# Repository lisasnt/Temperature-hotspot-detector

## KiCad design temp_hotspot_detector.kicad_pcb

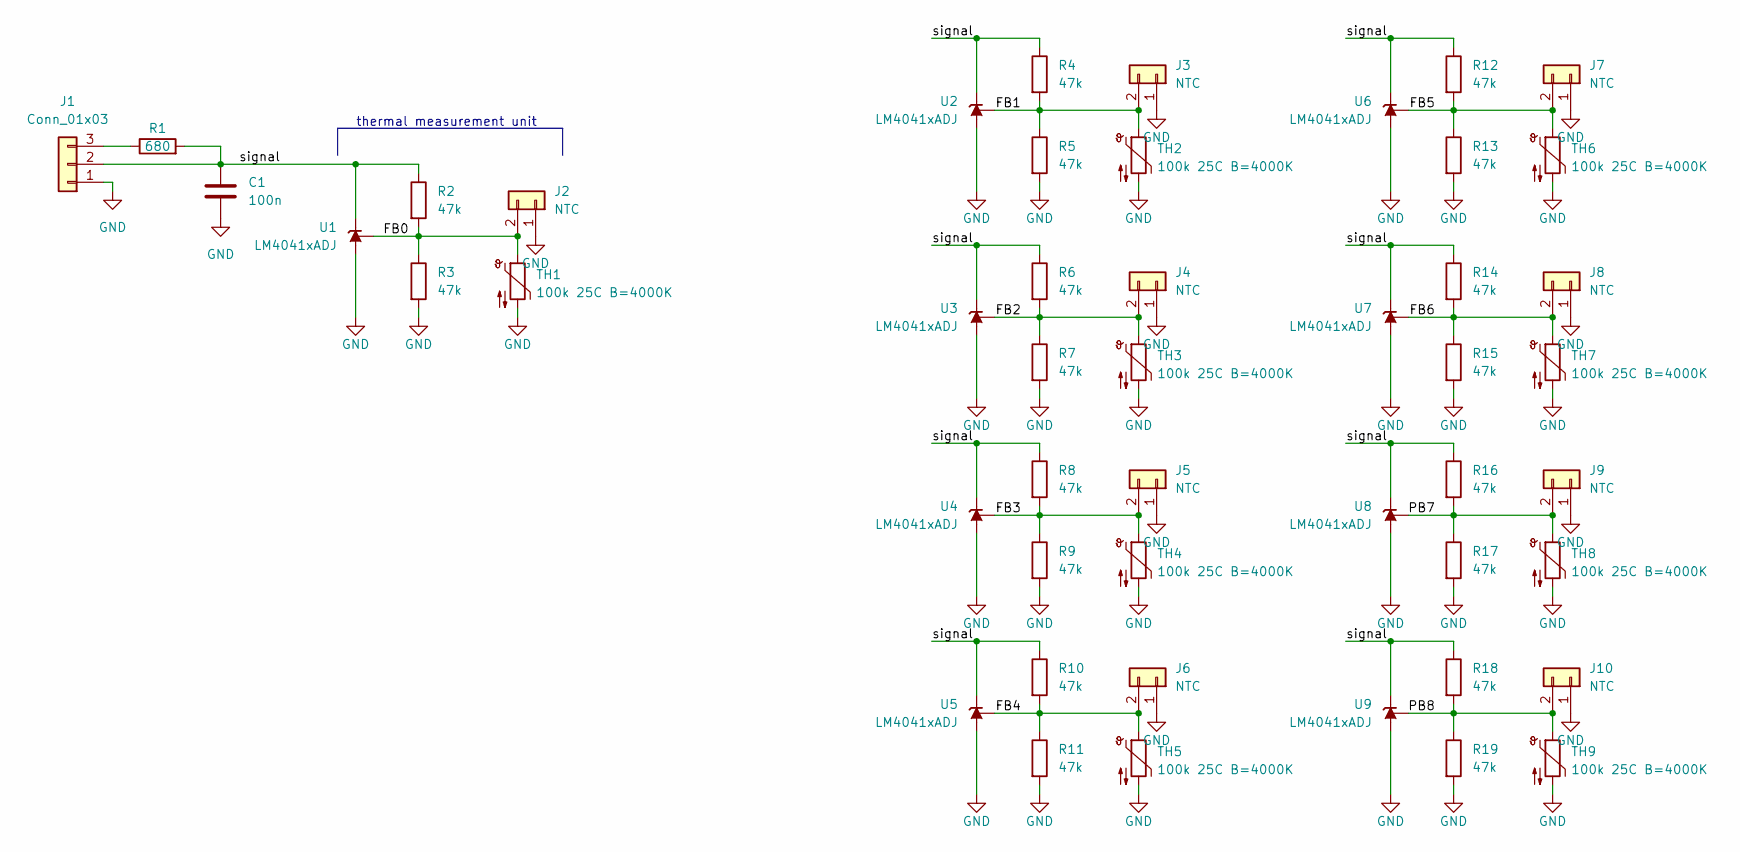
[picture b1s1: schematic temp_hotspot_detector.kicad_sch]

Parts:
C1: 100n; C_0603_1608Metric
J1: Conn_01x03; PinHeader_1x03_P2.54mm_Vertical
J2, J3, J4, J5, J6, J7, J8, J9, J10: NTC; PinHeader_1x02_P2.54mm_Vertical
R1: 680; R_0603_1608Metric
R2, R3, R4, R5, R6, R7, R8, R9, R10, R11, R12, R13, R14, R15, R16, R17, R18, R19: 47k; R_0603_1608Metric
TH1, TH2, TH3, TH4, TH5, TH6, TH7, TH8, TH9: 100k 25C B=4000K; R_0603_1608Metric
U1, U2, U3, U4, U5, U6, U7, U8, U9: LM4041xADJ; SOT-23

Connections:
/FB0: J2.2, R2.2, R3.1, TH1.1, U1.1 (REF)
/FB1: J3.2, R4.2, R5.1, TH2.1, U2.1 (REF)
/FB2: J4.2, R6.2, R7.1, TH3.1, U3.1 (REF)
/FB3: J5.2, R8.2, R9.1, TH4.1, U4.1 (REF)
/FB4: J6.2, R10.2, R11.1, TH5.1, U5.1 (REF)
/FB5: J7.2, R12.2, R13.1, TH6.1, U6.1 (REF)
/FB6: J8.2, R14.2, R15.1, TH7.1, U7.1 (REF)
/PB7: J9.2, R16.2, R17.1, TH8.1, U8.1 (REF)
/PB8: J10.2, R18.2, R19.1, TH9.1, U9.1 (REF)
/signal: C1.1, J1.2, R1.2, R2.1, R4.1, R6.1, R8.1, R10.1, R12.1, R14.1, R16.1, R18.1, U1.2 (K), U2.2 (K), U3.2 (K), U4.2 (K), U5.2 (K), U6.2 (K), U7.2 (K), U8.2 (K), U9.2 (K)
GND: C1.2, J1.1, J2.1, J3.1, J4.1, J5.1, J6.1, J7.1, J8.1, J9.1, J10.1, R3.2, R5.2, R7.2, R9.2, R11.2, R13.2, R15.2, R17.2, R19.2, TH1.2, TH2.2, TH3.2, TH4.2, TH5.2, TH6.2, TH7.2, TH8.2, TH9.2, U1.3 (A), U2.3 (A), U3.3 (A), U4.3 (A), U5.3 (A), U6.3 (A), U7.3 (A), U8.3 (A), U9.3 (A)
unnamed: J1.3, R1.1

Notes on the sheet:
thermal measurement unit

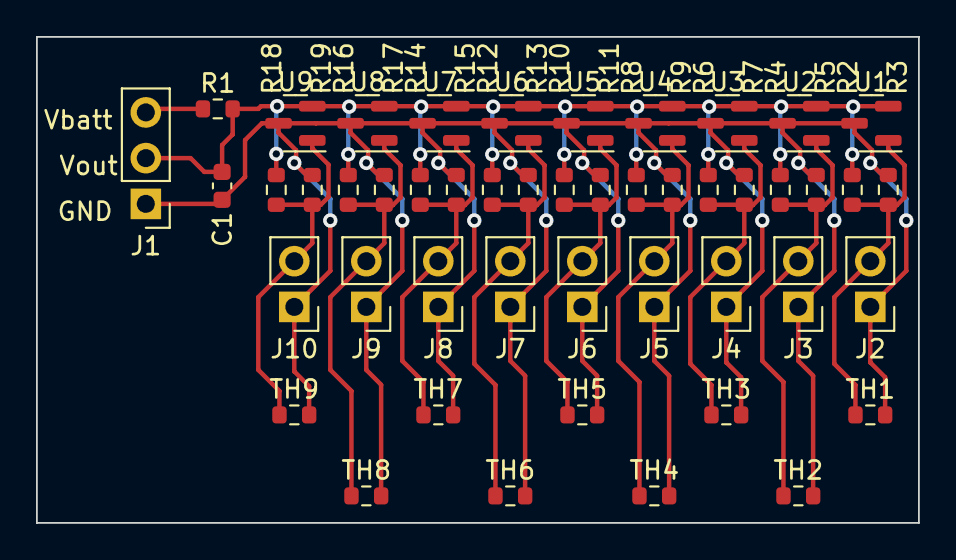
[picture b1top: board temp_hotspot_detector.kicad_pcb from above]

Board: 2 copper layers, 49.0 x 27.0 mm, 48 parts (0 on the bottom side), 12 nets.
